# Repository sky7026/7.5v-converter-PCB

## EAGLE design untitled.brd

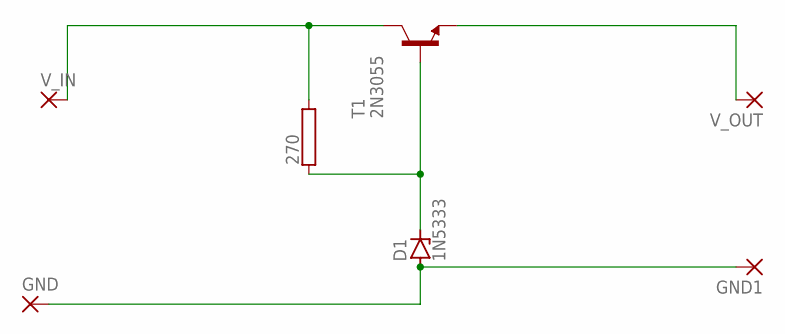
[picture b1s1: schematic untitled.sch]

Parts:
270: RMG100-V; TO-247-2V
D1: 1N5333; C1702-15
GND, GND1: 3,17/1,1
T1: 2N3055; TO3
V_IN: 3,17/1,1
V_OUT: 3,17/1,1

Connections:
unnamed: 270.2, T1.C, T1.C/ (C), V_IN.1
unnamed: 270.1, D1.C, T1.B
unnamed: T1.E, V_OUT.1
unnamed: D1.A, GND.1, GND1.1

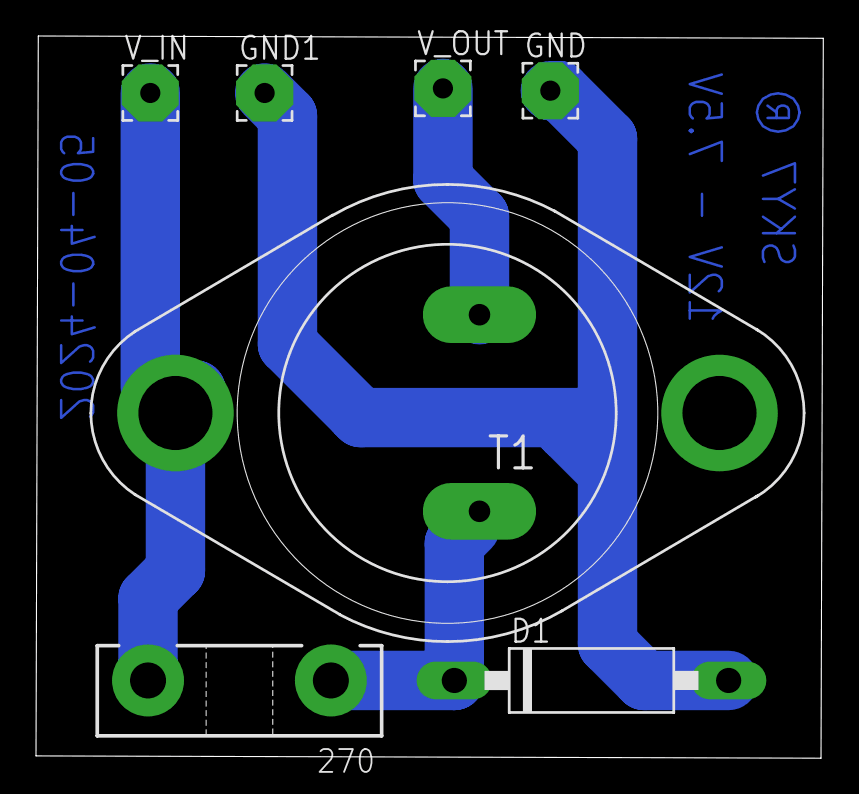
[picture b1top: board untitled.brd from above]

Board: 2 copper layers, 43.7 x 40.1 mm, 7 parts (0 on the bottom side), 4 nets.
